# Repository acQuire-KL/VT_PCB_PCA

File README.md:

HISTORY

<table>
  <tr>
    <td valign="top">
      
    </td>
    <td valign="top">
      <table border="1">
        <tr>
          <th style="font-size: 14px; font-weight: bold;">Name</th>
          <th style="font-size: 14px; font-weight: bold;">PCB</th>
          <th style="font-size: 14px; font-weight: bold;">PCA</th>
          <th style="font-size: 14px; font-weight: bold;">Date</th>
          <th style="font-size: 14px; font-weight: bold;">Comments</th>
        </tr>
        <tr>
          
          <td style="font-size: 12px;">ADE</td>
          <td style="font-size: 12px;">4901-30030-05</td>
          <td style="font-size: 12px;">3901-30030-05</td>
          <td style="font-size: 12px;">2024-09-20</td>
          <td style="font-size: 12px;">Current MFG Revisions</td>
        </tr>
        <tr>
          <td style="font-size: 12px;"></td>
          <td style="font-size: 12px;">2025-03-28</td>
          <td style="font-size: 12px;">00 --> 01 to add new circuit sections</td>
        </tr>
        <tr>
          <td style="font-size: 12px;">PCB_1001_00</td>
          <td style="font-size: 12px;">2025-03-01</td>
          <td style="font-size: 12px;">Initial release</td>
        </tr>
      </table>
    </td>
  </tr>
</table>

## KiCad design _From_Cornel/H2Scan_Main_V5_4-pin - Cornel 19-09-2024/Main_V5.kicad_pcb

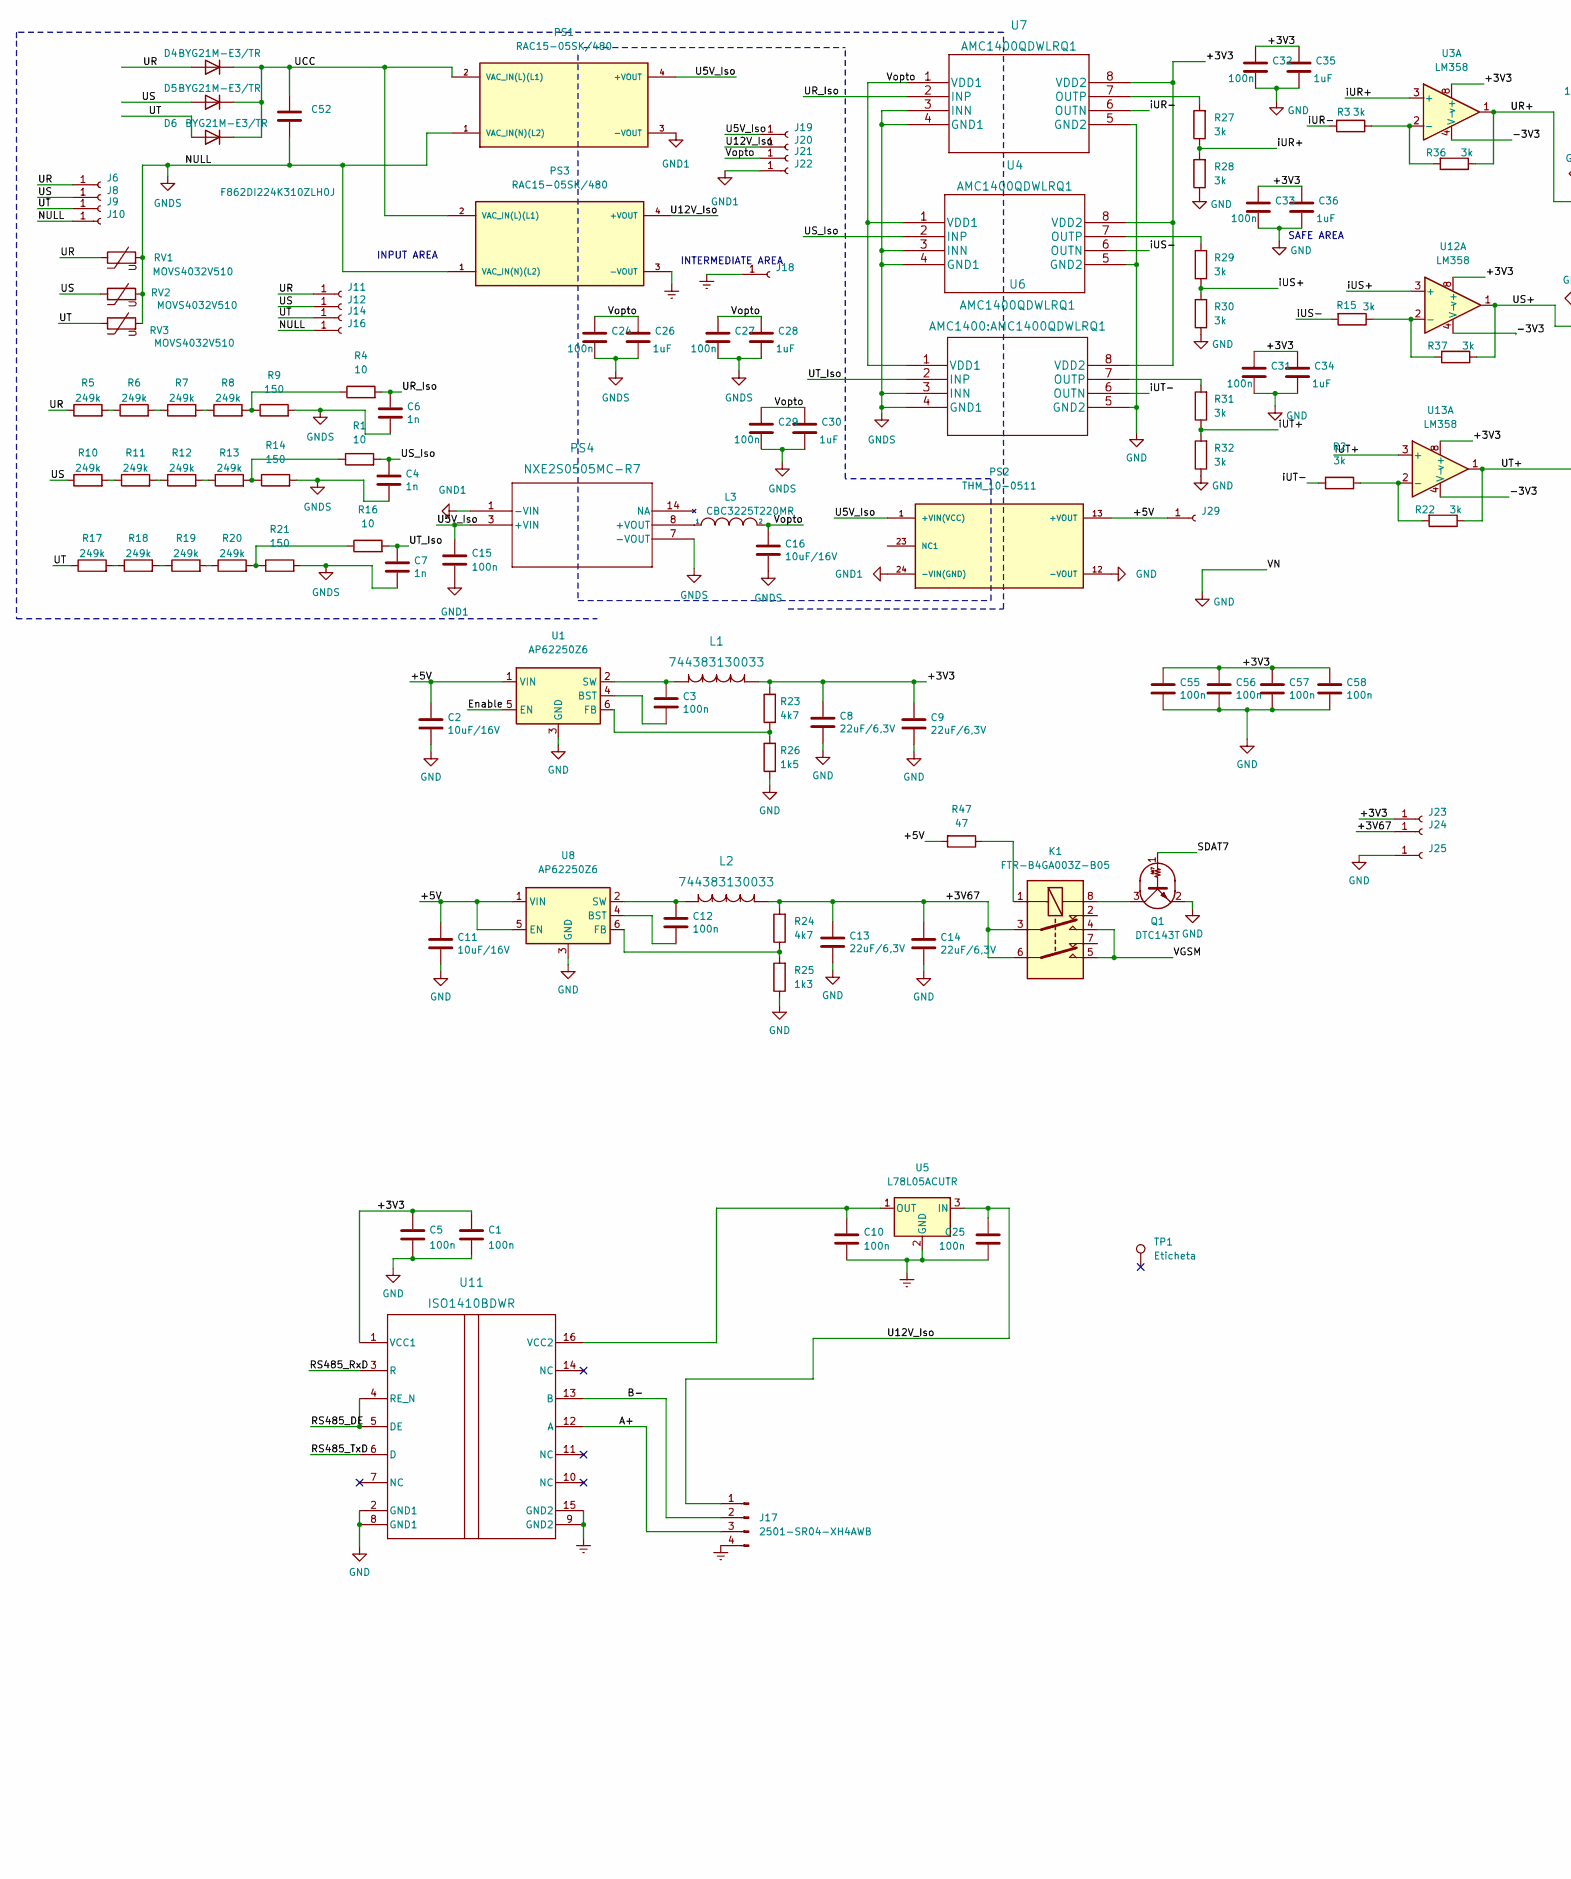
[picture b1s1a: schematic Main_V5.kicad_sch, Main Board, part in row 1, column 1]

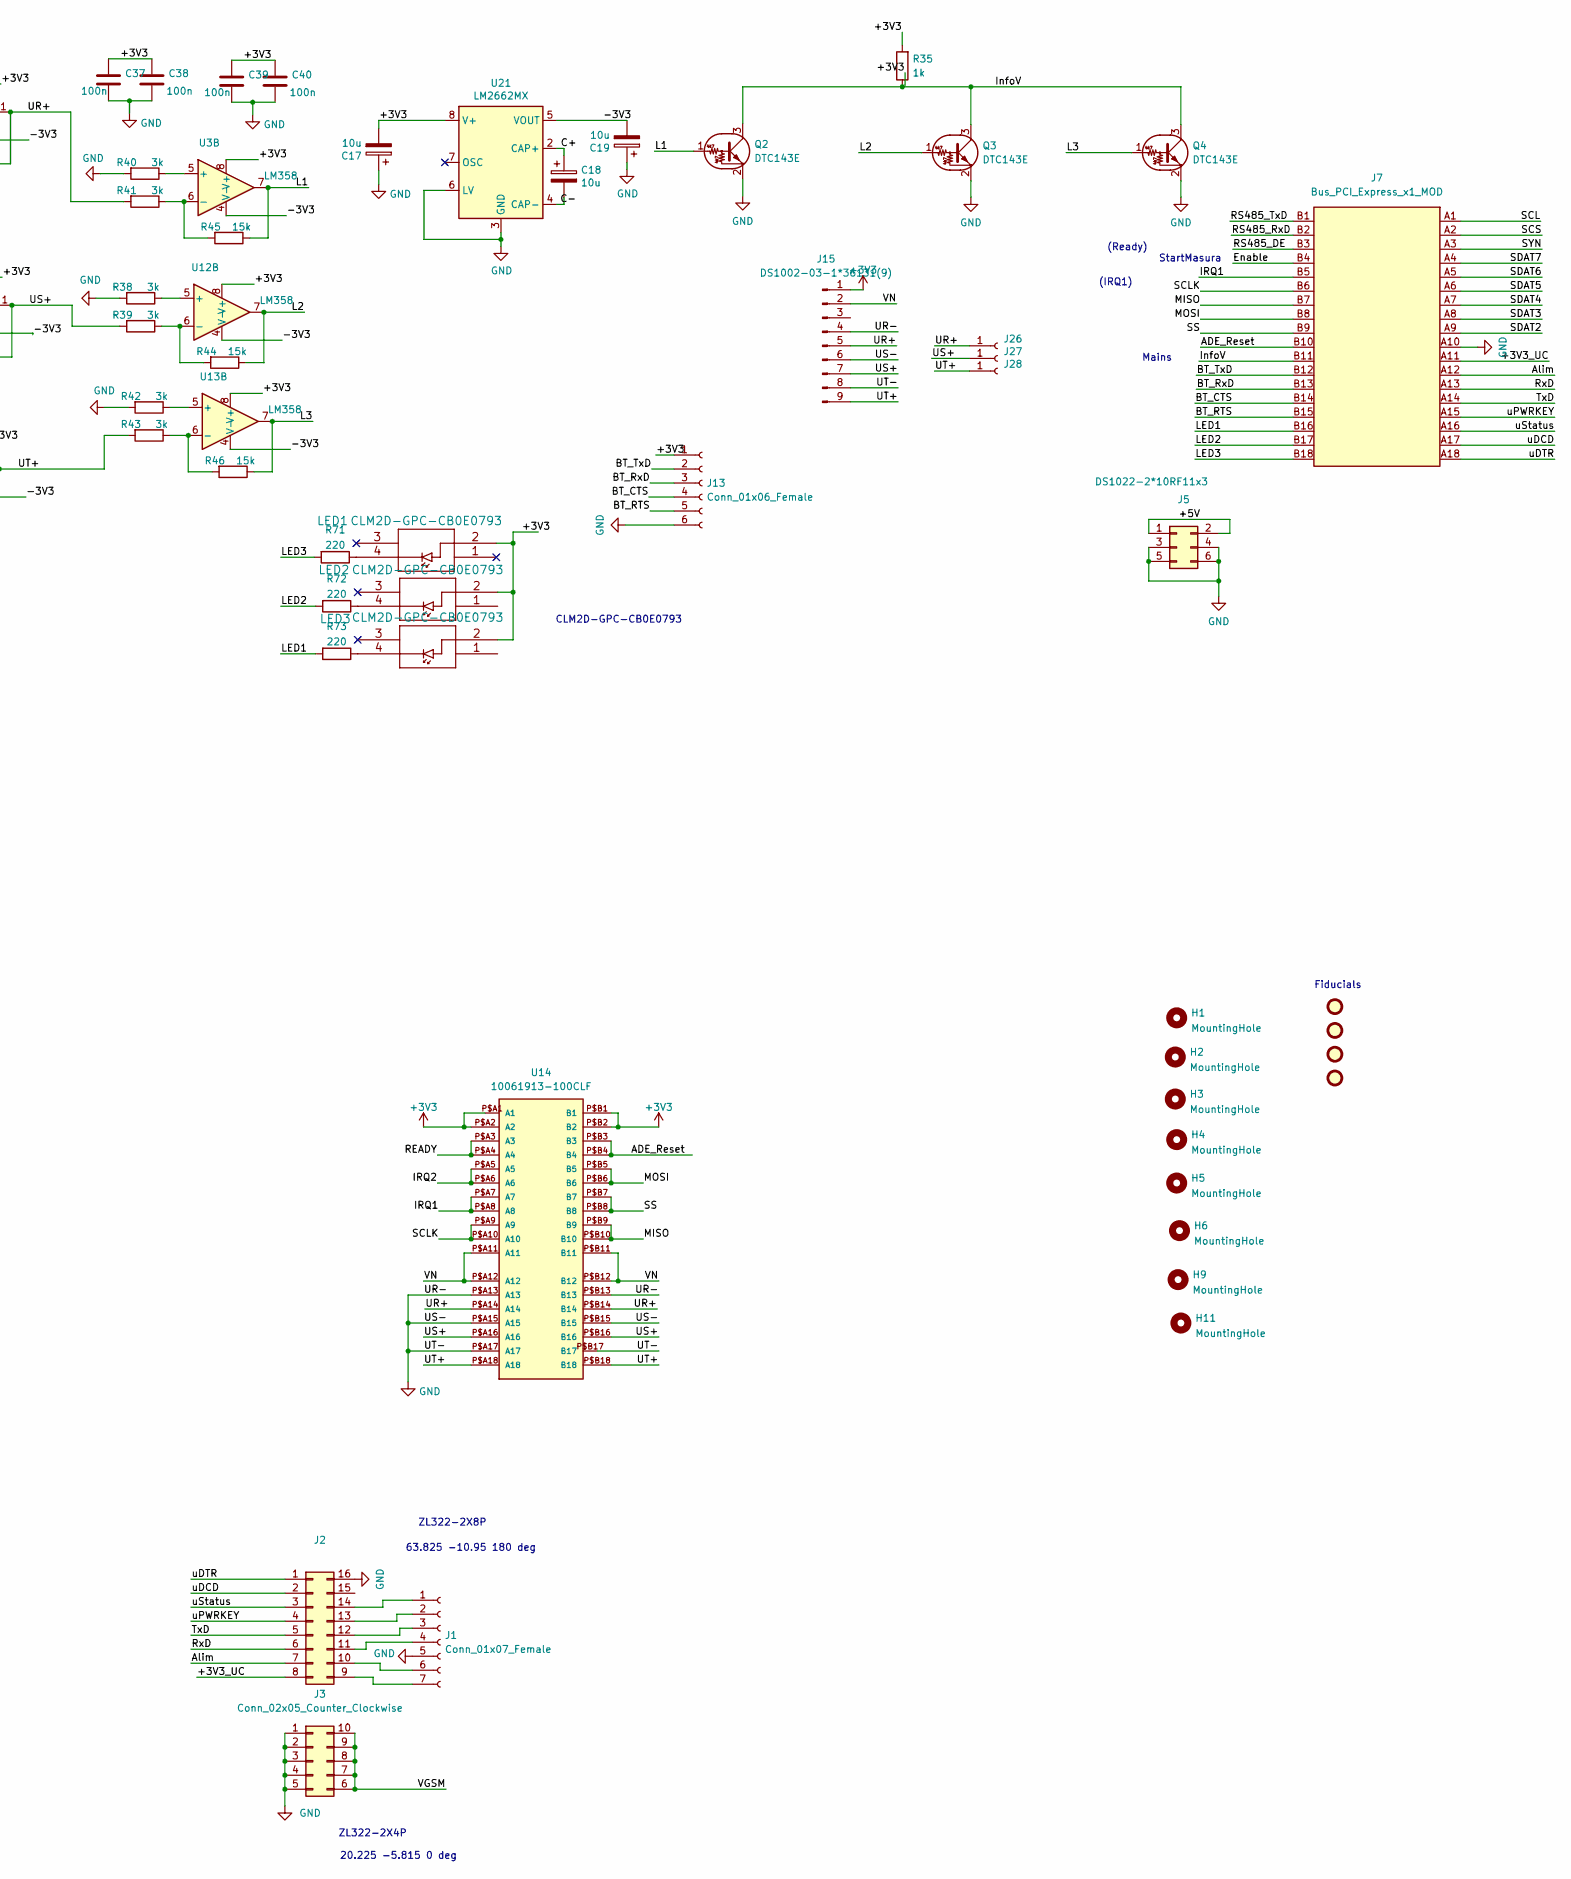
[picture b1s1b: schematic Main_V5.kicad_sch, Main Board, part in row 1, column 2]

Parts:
C1, C3, C5, C10, C12, C15, C24, C25, C27, C29, C31, C32, C33, C37, C38, C39, C40, C55, C56, C57, C58: 100n; C_0603_1608Metric
C2, C11, C16: 10uF/16V; C_1206_3216Metric
C4, C6, C7: 1n; C_0603_1608Metric
C8, C9, C13, C14: 22uF/6,3V; C_1206_3216Metric
C17, C18, C19: 10u; C_1206_3216Metric
C26, C28, C30, C34, C35, C36: 1uF; C_0603_1608Metric
C52: F862DI224K310ZLH0J; C_Rect_L24.0mm_W7.0mm_P22.50mm_MKT
D4, D5, D6: BYG21M-E3/TR; D_SMA
FID1, FID2, FID3, FID4: Fiducial; Fiducial_1mm_Mask2mm
H1, H2, H3, H4, H5, H6, H9, H11: MountingHole; MountingHole_3.2mm_M3
J1: Conn_01x07_Female; PinSocket_1x07_P2.54mm_Vertical
J2: Conn_02x08_Counter_Clockwise; PinSocket_2x08_P2.54mm_Vertical_SMD_MOD
J3: Conn_02x05_Counter_Clockwise; PinSocket_2x05_P2.54mm_Vertical_SMD
J5: DS1022-2*10RF11x3; PinHeader_2x03_P2.54mm_Horizontal
J6: Conn_01x01_Female; DELTA_SolderWire-1.5sqmm_1x01_D1.7mm_OD3.9mm
J7: Bus_PCI_Express_x1_MOD; BUS_PCIexpress_x1
J8, J9, J10: Conn_01x01_Female; DELTA_R_SolderWire-1.5sqmm_1x01_D1.7mm_OD3.9mm
J11, J12, J14, J16, J18, J19, J20, J21, J22, J23, J24, J25, J26, J27, J28, J29: Conn_01x01_Female; TestPoint_Pad_2.5x2.5mm_Delta
J13: Conn_01x06_Female; PinSocket_1x06_P2.54mm_Vertical
J15: DS1002-03-1*36131(9); PinSocket_1x09_P2.54mm_Vertical
J17: 2501-SR04-XH4AWB; A2501-SR04-XH4AWB
K1: FTR-B4GA003Z-B05; Relay_Fujitsu_FTR-B4GA003
L1, L2: 744383130033
L3: CBC3225T220MR; L_1206_3216Metric
LED1, LED2, LED3: CLM2D-GPC-CB0E0793
PS1, PS3: RAC15-05SK/480; CONV_RAC15-12SK_480; PARTREV 0/2022
PS2: THM_10-0511; CONV_THM_10-0511; PARTREV Jan 06, 2021
PS4: NXE2S0505MC-R7; NXE2_SINGLE_SURFACE_MUR
Q1: DTC143T; SOT-23
Q2, Q3, Q4: DTC143E; SOT-23
R1, R4, R16: 10; R_0603_1608Metric
R2, R3, R15, R22, R27, R28, R29, R30, R31, R32, R36, R37, R38, R39, R40, R41, R42, R43: 3k; R_0603_1608Metric
R5, R6, R7, R8, R10, R11, R12, R13, R17, R18, R19, R20: 249k; R_2512_6332Metric
R9, R14, R21: 150; R_0603_1608Metric
R23, R24: 4k7; R_0603_1608Metric
R25: 1k3; R_0603_1608Metric
R26: 1k5; R_0603_1608Metric
R35: 1k; R_0603_1608Metric
R44, R45, R46: 15k; R_0603_1608Metric
R47: 47; R_0603_1608Metric
R71, R72, R73: 220; R_0603_1608Metric
RV1, RV2, RV3: MOVS4032V510; MOVS4032V460
TP1: Eticheta
U1, U8: AP62250Z6; SOT-563
U3, U12, U13: LM358; SO-8_3.9x4.9mm_P1.27mm
U4, U6, U7: AMC1400QDWLRQ1
U5: L78L05ACUTR; SOT-89-3
U11: ISO1410BDWR; DW0016B_HV
U14: 10061913-100CLF; MPN 10061913-100CLF
U21: LM2662MX; SO-8_3.9x4.9mm_P1.27mm

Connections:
+3V3: C1.1, C5.1, C8.1, C9.1, C17.2, C31.1, C32.1, C33.1, C34.1, C35.1, C36.1, C37.1, C38.1, C39.1, C40.1, C55.1, C56.1, C57.1, C58.1, J13.1, J15.1, J23.1, L1.1, LED1.2, LED2.2, LED3.2, R23.2, R35.2, U3.8 (v+), U4.8 (VDD2), U6.8 (VDD2), U7.8 (VDD2), U11.1 (VCC1), U12.8 (v+), U13.8 (v+), U14.P$A1 (A1), U14.P$A2 (A2), U14.P$B1 (B1), U14.P$B2 (B2), U21.8 (V+)
/+3V3_UC: J2.8, J7.A11
/+3V67: C13.1, C14.1, J24.1, K1.3, K1.6, L2.1, R24.2
/+5V: C2.1, C11.1, J5.1, J5.2, J29.1, PS2.13 (+VOUT), R47.2, U1.1 (VIN), U8.1 (VIN), U8.5 (EN)
/-3V3: C19.2, U3.4 (V-), U12.4 (V-), U13.4 (V-), U21.5 (VOUT)
/A+: J17.3, U11.12 (A)
/ADE_Reset: J7.B10, U14.P$B3 (B3), U14.P$B4 (B4)
/Alim: J2.7, J7.A12
/B-: J17.2, U11.13 (B)
/BT_CTS: J7.B14, J13.4
/BT_RTS: J7.B15, J13.5
/BT_RxD: J7.B13, J13.3
/BT_TxD: J7.B12, J13.2
/C+: C18.1, U21.2 (CAP+)
/C-: C18.2, U21.4 (CAP-)
/Enable: J7.B4, U1.5 (EN)
/IRQ1: J7.B5, U14.P$A7 (A7), U14.P$A8 (A8)
/IRQ2: U14.P$A5 (A5), U14.P$A6 (A6)
/InfoV: J7.B11, Q2.3 (C), Q3.3 (C), Q4.3 (C), R35.1
/L1: Q2.1 (B), R45.1, U3.7
/L2: Q3.1 (B), R44.1, U12.7
/L3: Q4.1 (B), R46.1, U13.7
/LED1: J7.B16, R73.2
/LED2: J7.B17, R72.2
/LED3: J7.B18, R71.2
/MISO: J7.B7, U14.P$B9 (B9), U14.P$B10 (B10)
/MOSI: J7.B8, U14.P$B5 (B5), U14.P$B6 (B6)
/READY: U14.P$A3 (A3), U14.P$A4 (A4)
/RS485_DE: J7.B3, U11.4 (RE_N), U11.5 (DE)
/RS485_RxD: J7.B2, U11.3 (R)
/RS485_TxD: J7.B1, U11.6 (D)
/RxD: J2.6, J7.A13
/SCL: J7.A1
/SCLK: J7.B6, U14.P$A9 (A9), U14.P$A10 (A10)
/SCS: J7.A2
/SDAT2: J7.A9
/SDAT3: J7.A8
/SDAT4: J7.A7
/SDAT5: J7.A6
/SDAT6: J7.A5
/SDAT7: J7.A4, Q1.1 (B)
/SS: J7.B9, U14.P$B7 (B7), U14.P$B8 (B8)
/SYN: J7.A3
/TxD: J2.5, J7.A14
/U5V_Iso: C15.1, J19.1, PS1.4 (+VOUT), PS2.1 (+VIN(VCC)), PS4.3 (+VIN)
/U12V_Iso: C25.1, J17.1, J20.1, PS3.4 (+VOUT), U5.3 (IN)
/UCC: C52.1, D4.1 (K), D5.1 (K), D6.1 (K), PS1.2 (VAC_IN(L)(L1)), PS3.2 (VAC_IN(L)(L1))
/UR: D4.2 (A), J6.1, J11.1, R5.1, RV1.1
/UR+: J15.5, J26.1, R36.1, R41.2, U3.1, U14.P$A14 (A14), U14.P$B14 (B14)
/UR_Iso: C6.1, R4.2, U7.2 (INP)
/US: D5.2 (A), J8.1, J12.1, R10.1, RV2.1
/US+: J15.7, J27.1, R37.1, R39.2, U12.1, U14.P$A16 (A16), U14.P$B16 (B16)
/US_Iso: C4.1, R1.2, U4.2 (INP)
/UT: D6.2 (A), J9.1, J14.1, R17.1, RV3.1
/UT+: J15.9, J28.1, R22.1, R43.2, U13.1, U14.P$A18 (A18), U14.P$B18 (B18)
/UT_Iso: C7.1, R16.2, U6.2 (INP)
/VGSM: J3.6, J3.7, J3.8, J3.9, J3.10, K1.4, K1.5
/Vopto: C16.1, C24.1, C26.1, C27.1, C28.1, C29.1, C30.1, J21.1, L3.2, U4.1 (VDD1), U6.1 (VDD1), U7.1 (VDD1)
/iUR+: R27.1, R28.2, U3.3 (+)
/iUR-: R3.2, U7.6 (OUTN)
/iUS+: R29.1, R30.2, U12.3 (+)
/iUS-: R15.2, U4.6 (OUTN)
/iUT+: R31.1, R32.2, U13.3 (+)
/iUT-: R2.2, U6.6 (OUTN)
/uDCD: J2.2, J7.A17
/uDTR: J2.1, J7.A18
/uPWRKEY: J2.4, J7.A15
/uStatus: J2.3, J7.A16
Earth: C10.2, C25.2, J17.4, J18.1, PS3.3 (-VOUT), U5.2 (GND), U11.9 (GND2), U11.15 (GND2)
GND: C1.2, C2.2, C5.2, C8.2, C9.2, C11.2, C13.2, C14.2, C17.1, C19.1, C31.2, C32.2, C33.2, C34.2, C35.2, C36.2, C37.2, C38.2, C39.2, C40.2, C55.2, C56.2, C57.2, C58.2, J1.5, J2.16, J3.1, J3.2, J3.3, J3.4, J3.5, J5.3, J5.4, J5.5, J5.6, J7.A10, J13.6, J15.2, J15.4, J15.6, J15.8, J25.1, PS2.12 (-VOUT), Q1.2 (E), Q2.2 (E), Q3.2 (E), Q4.2 (E), R25.1, R26.1, R28.1, R30.1, R32.1, R38.2, R40.2, R42.2, U1.3 (GND), U4.5 (GND2), U6.5 (GND2), U7.5 (GND2), U8.3 (GND), U11.2 (GND1), U11.8 (GND1), U14.P$A11 (A11), U14.P$A12 (A12), U14.P$A13 (A13), U14.P$A15 (A15), U14.P$A17 (A17), U14.P$B11 (B11), U14.P$B12 (B12), U14.P$B13 (B13), U14.P$B15 (B15), U14.P$B17 (B17), U21.3 (GND), U21.6 (LV)
GND1: C15.2, J22.1, PS1.3 (-VOUT), PS2.24 (-VIN(GND)), PS4.1 (-VIN)
GNDS: C4.2, C6.2, C7.2, C16.2, C24.2, C26.2, C27.2, C28.2, C29.2, C30.2, C52.2, J10.1, J16.1, PS1.1 (VAC_IN(N)(L2)), PS3.1 (VAC_IN(N)(L2)), PS4.7 (-VOUT), R9.2, R14.2, R21.2, RV1.2, RV2.2, RV3.2, U4.3 (INN), U4.4 (GND1), U6.3 (INN), U6.4 (GND1), U7.3 (INN), U7.4 (GND1)
unnamed: J1.1, J2.14
unnamed: J1.2, J2.13
unnamed: J1.3, J2.12
unnamed: J1.4, J2.11
unnamed: J1.6, J2.10
unnamed: J1.7, J2.9
unnamed: K1.1, R47.1
unnamed: LED1.4, R71.1
unnamed: LED2.4, R72.1
unnamed: LED3.4, R73.1
unnamed: L3.1, PS4.8 (+VOUT)
unnamed: K1.8, Q1.3 (C)
unnamed: R1.1, R13.2, R14.1
unnamed: R4.1, R8.2, R9.1
unnamed: R5.2, R6.1
unnamed: R6.2, R7.1
unnamed: R7.2, R8.1
unnamed: R10.2, R11.1
unnamed: R11.2, R12.1
unnamed: R12.2, R13.1
unnamed: R16.1, R20.2, R21.1
unnamed: R17.2, R18.1
unnamed: R18.2, R19.1
unnamed: R19.2, R20.1
unnamed: C3.2, U1.4 (BST)
unnamed: R23.1, R26.2, U1.6 (FB)
unnamed: C3.1, L1.2, U1.2 (SW)
unnamed: R3.1, R36.2, U3.2 (-)
unnamed: R40.1, U3.5 (+)
unnamed: R41.1, R45.2, U3.6 (-)
unnamed: R29.2, U4.7 (OUTP)
unnamed: R31.2, U6.7 (OUTP)
unnamed: R27.2, U7.7 (OUTP)
unnamed: C12.2, U8.4 (BST)
unnamed: R24.1, R25.2, U8.6 (FB)
unnamed: C12.1, L2.2, U8.2 (SW)
unnamed: C10.1, U5.1 (OUT), U11.16 (VCC2)
unnamed: R15.1, R37.2, U12.2 (-)
unnamed: R38.1, U12.5 (+)
unnamed: R39.1, R44.2, U12.6 (-)
unnamed: R2.1, R22.2, U13.2 (-)
unnamed: R42.1, U13.5 (+)
unnamed: R43.1, R46.2, U13.6 (-)

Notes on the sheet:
ZL322-2X4P
ZL322-2X8P
20.225 -5.815 0 deg
(Ready)
Fiducials
Mains
(IRQ1)
CLM2D-GPC-CB0E0793
StartMasura
63.825 -10.95 180 deg
SAFE AREA
INPUT AREA
INTERMEDIATE AREA

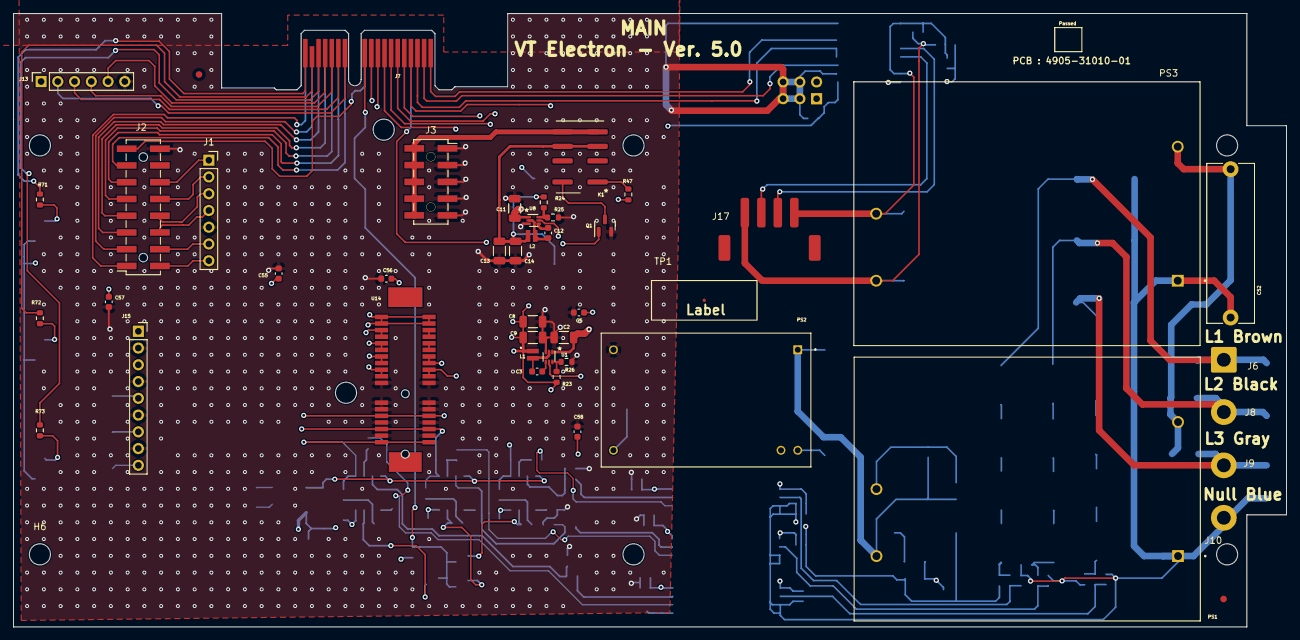
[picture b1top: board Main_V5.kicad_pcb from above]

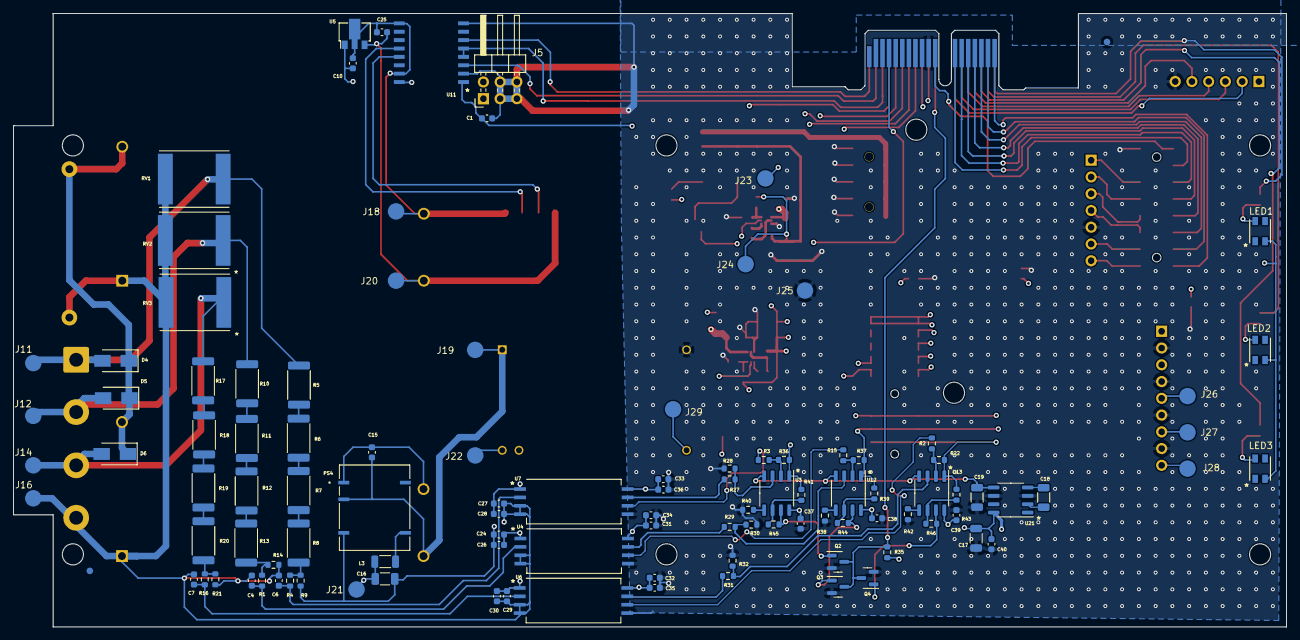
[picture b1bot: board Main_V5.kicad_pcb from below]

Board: 4 copper layers, 193.0 x 93.0 mm, 163 parts (109 on the bottom side), 107 nets.

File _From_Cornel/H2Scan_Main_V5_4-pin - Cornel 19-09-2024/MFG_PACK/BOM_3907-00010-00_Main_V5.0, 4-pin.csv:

"Reference","VTPN","Value","Datasheet","Footprint","Qty","DNP"
"C1,C3,C5,C10,C12,C15,C24,C25,C27,C29,C31,C32,C33,C37,C38,C39,C40,C55,C56,C57,C58","4106-00020-00","100n","~","Capacitor_SMD:C_0603_1608Metric","21",""
"C2,C11,C16","4112-00100-00","10uF/16V","~","Capacitor_SMD:C_1206_3216Metric","3",""
"C4,C6,C7","4106-00030-00","1n","~","Capacitor_SMD:C_0603_1608Metric","3",""
"C8,C9,C13,C14","4112-00150-00","22uF/6,3V","~","Capacitor_SMD:C_1206_3216Metric","4",""
"C17,C18,C19","4112-00110-00","10u","~","Capacitor_SMD:C_1206_3216Metric","3",""
"C26,C28,C30,C34,C35,C36","4106-00100-00","1uF","~","Capacitor_SMD:C_0603_1608Metric","6",""
"C52","4130-00010-00","F862DI224K310ZLH0J","~","Capacitor_THT:C_Rect_L24.0mm_W7.0mm_P22.50mm_MKT","1",""
"D4,D5,D6","4510-00010-00","BYG21M-E3/TR","~","Diode_SMD:D_SMA","3",""
"FID1,FID2,FID3,FID4","4000-00000-00","Fiducial","~","Fiducial:Fiducial_1mm_Mask2mm","4",""
"H1,H2,H3,H4,H5,H6,H9,H11","4000-00000-00","MountingHole","~","MountingHole:MountingHole_3.2mm_M3","8",""
"J1","4401-00070-00","Conn_01x07_Female","~","Connector_PinSocket_2.54mm:PinSocket_1x07_P2.54mm_Vertical","1",""
"J2","4402-10021-00","Conn_02x08_Counter_Clockwise","~","Connector_PinSocket_2.54mm:PinSocket_2x08_P2.54mm_Vertical_SMD_MOD","1",""
"J3","4402-10011-00","Conn_02x05_Counter_Clockwise","~","Connector_PinSocket_2.54mm:PinSocket_2x05_P2.54mm_Vertical_SMD","1",""
"J5","4400-00010-00","DS1022-2*10RF11x3","~","Connector_PinHeader_2.54mm:PinHeader_2x03_P2.54mm_Horizontal","1",""
"J6,J8,J9,J10,J11,J12,J14,J16,J18,J19,J20,J21,J22,J23,J24,J25,J26,J27,J28,J29","4000-00000-00","Conn_01x01_Female","~","-- mixed values --","20",""
"J7","4000-00000-00","Bus_PCI_Express_x1_MOD","http://www.ritrontek.com/uploadfile/2016/1026/20161026105231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","Connector_PCBEdge:BUS_PCIexpress_x1","1",""
"J13","4401-00050-00","Conn_01x06_Female","~","Connector_PinSocket_2.54mm:PinSocket_1x06_P2.54mm_Vertical","1",""
"J15","4401-00060-00","DS1002-03-1*36131(9)","~","Connector_PinSocket_2.54mm:PinSocket_1x09_P2.54mm_Vertical","1",""
"J17","4408-00030-00","2501-SR04-XH4AWB","~","Connector_JST:A2501-SR04-XH4AWB","1",""
"K1","4750-00010-00","FTR-B4GA003Z-B05","https://www.fujitsu.com/downloads/MICRO/fcai/relays/ftr-f1.pdf","Relay_SMD:Relay_Fujitsu_FTR-B4GA003","1",""
"L1,L2","4300-00010-00","744383130033","","Inductanta744:744383130033","2",""
"L3","4300-00020-00","CBC3225T220MR","~","Inductor_SMD:L_1206_3216Metric","1",""
"LED1,LED2,LED3","4752-00010-00","CLM2D-GPC-CB0E0793","","LedSMD_Cree:CLM2D-GPC-CB0E0793","3",""
"PS1,PS3","4520-30010-00","RAC15-05SK/480","","RAC15:CONV_RAC15-12SK_480","2",""
"PS2","4520-20010-00","THM_10-0511","","THM 10-0511:CONV_THM_10-0511","1",""
"PS4","4520-20022-00","NXE2S0505MC-R7","NXE2S0505MC-R7","NXE2S0505MC-R7:NXE2_SINGLE_SURFACE_MUR","1",""
"Q1","4500-00020-00","DTC143T","","Package_TO_SOT_SMD:SOT-23","1",""
"Q2,Q3,Q4","4500-00010-00","DTC143E","","Package_TO_SOT_SMD:SOT-23","3",""
"R1,R4,R16","4006-00030-00","10","~","Resistor_SMD:R_0603_1608Metric","3",""
"R2,R3,R15,R22,R27,R28,R29,R30,R31,R32,R36,R37,R38,R39,R40,R41,R42,R43","4006-00300-00","3k","~","Resistor_SMD:R_0603_1608Metric","18",""
"R5,R6,R7,R8,R10,R11,R12,R13,R17,R18,R19,R20","4018-01000-00","249k","~","Resistor_SMD:R_2512_6332Metric","12",""
"R9,R14,R21","4006-00040-00","150","~","Resistor_SMD:R_0603_1608Metric","3",""
"R23,R24","4006-00150-00","4k7","~","Resistor_SMD:R_0603_1608Metric","2",""
"R25","4006-00130-00","1k3","~","Resistor_SMD:R_0603_1608Metric","1",""
"R26","4006-00140-00","1k5","~","Resistor_SMD:R_0603_1608Metric","1",""
"R35","4006-00100-00","1k","~","Resistor_SMD:R_0603_1608Metric","1",""
"R44,R45,R46","4006-00160-00","15k","~","Resistor_SMD:R_0603_1608Metric","3",""
"R47","4006-00010-00","47","~","Resistor_SMD:R_0603_1608Metric","1",""
"R71,R72,R73","4006-00020-00","220","~","Resistor_SMD:R_0603_1608Metric","3",""
"RV1,RV2,RV3","4022-00010-00","MOVS4032V510","~","MOVS4032V510:MOVS4032V460","3",""
"TP1","4000-00000-00","Eticheta","~","Symbol:Eticheta","1",""
"U1,U8","4520-10010-00","AP62250Z6","https://www.diodes.com/assets/Datasheets/AP62250.pdf","Package_TO_SOT_SMD:SOT-563","2",""
"U3,U12,U13","4708-00021-00","LM358","http://www.ti.com/lit/ds/symlink/lm2904-n.pdf","Package_SO:SO-8_3.9x4.9mm_P1.27mm","3",""
"U4,U6,U7","4710-00010-00","AMC1400QDWLRQ1","","AMC1400:AMC1400QDWLRQ1","3",""
"U5","4522-00010-00","L78L05ACUTR","http://www.st.com/content/ccc/resource/technical/document/da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","Package_TO_SOT_SMD:SOT-89-3","1",""
"U11","4700-00020-00","ISO1410BDWR","ISO1410BDWR","ISO1410:DW0016B_HV","1",""
"U14","4410-00010-00","10061913-100CLF","","PCI_SMD_MOD:10061913-100CLF","1",""
"U21","4520-00020-01","LM2662MX","http://www.ti.com/lit/ds/symlink/lmc7660.pdf","Package_SO:SO-8_3.9x4.9mm_P1.27mm","1",""

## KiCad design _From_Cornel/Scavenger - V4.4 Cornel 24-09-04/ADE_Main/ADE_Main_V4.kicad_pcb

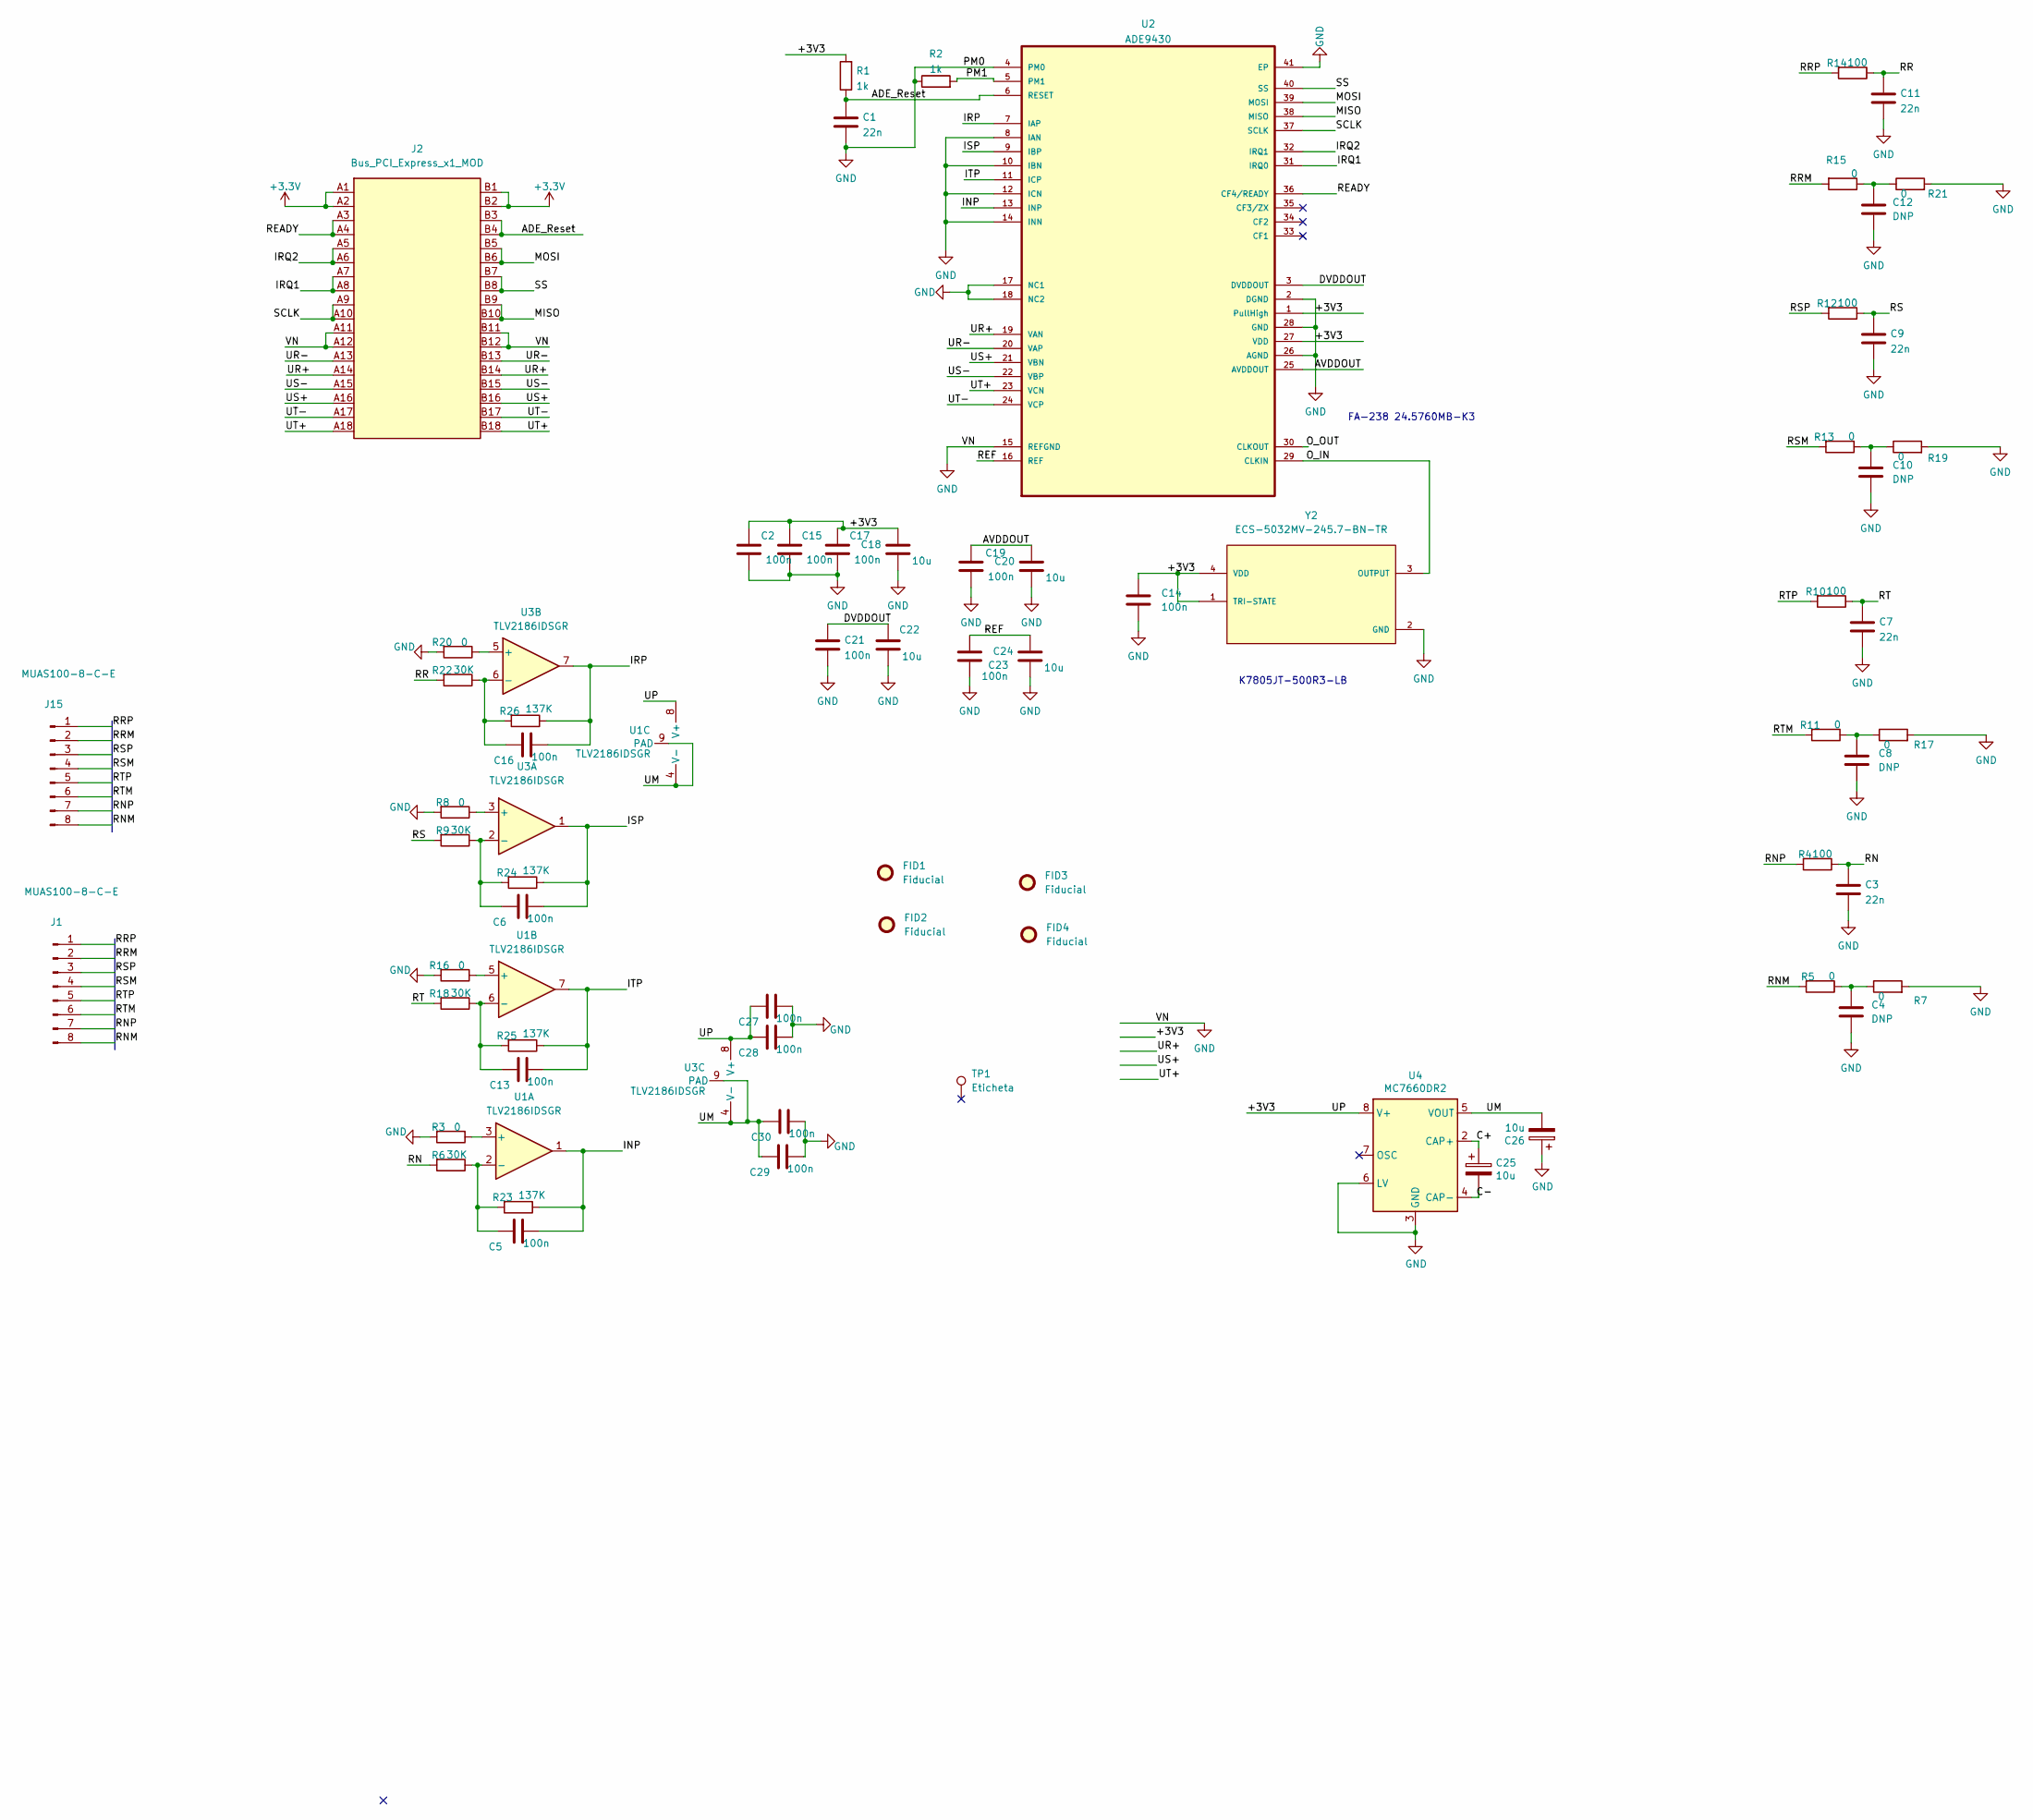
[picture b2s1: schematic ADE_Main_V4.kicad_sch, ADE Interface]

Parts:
C1, C3, C7, C9, C11: 22n; C_0402_1005Metric
C2: 100n; C_0603_1608Metric
C4, C8, C10, C12: DNP; C_0402_1005Metric
C5, C6, C13, C14, C15, C16, C17, C19, C21, C23, C27, C28, C29, C30: 100n; C_0402_1005Metric
C18, C20, C22, C24, C25, C26: 10u; C_1206_3216Metric
FID1, FID2, FID3, FID4: Fiducial; Fiducial_1mm_Mask2mm
J1: MUAS100-8-C-E; A2501-SR08-XH8AWB
J2: Bus_PCI_Express_x1_MOD; BUS_PCIexpress_x1
J15: MUAS100-8-C-E; PinHeader_1x08_P2.54mm_Vertical
R1, R2: 1k; R_0402_1005Metric
R3, R5, R7, R8, R11, R13, R15, R16, R17, R19, R20, R21: 0; R_0402_1005Metric
R4, R10, R12, R14: 100; R_0402_1005Metric
R6, R9, R18, R22: 30K; R_0402_1005Metric
R23, R24, R25, R26: 137K; R_0402_1005Metric
TP1: Eticheta
U1, U3: TLV2186IDSGR; WSON-8-1EP_2x2mm_P0.5mm_EP0.9x1.6mm_ThermalVias
U2: ADE9430; MPN AD9115BCPZ
U4: MC7660DR2; SO-8_3.9x4.9mm_P1.27mm
Y2: ECS-5032MV-245.7-BN-TR; OSC_ECS-5032MV-245.7-BN-TR

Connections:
/ADE_Reset: C1.1, J2.B3, J2.B4, R1.1, U2.6 (RESET)
/AVDDOUT: C19.1, C20.1, U2.25 (AVDDOUT)
/C+: C25.1, U4.2 (CAP+)
/C-: C25.2, U4.4 (CAP-)
/DVDDOUT: C21.1, C22.1, U2.3 (DVDDOUT)
/INP: C5.1, R23.1, U1.1, U2.13 (INP)
/IRP: C16.1, R26.1, U2.7 (IAP), U3.7
/IRQ1: J2.A7, J2.A8, U2.31 (IRQ0)
/IRQ2: J2.A5, J2.A6, U2.32 (IRQ1)
/ISP: C6.1, R24.1, U2.9 (IBP), U3.1
/ITP: C13.1, R25.1, U1.7, U2.11 (ICP)
/MISO: J2.B9, J2.B10, U2.38 (MISO)
/MOSI: J2.B5, J2.B6, U2.39 (MOSI)
/O_IN: U2.29 (CLKIN), Y2.3 (OUTPUT)
/O_OUT: U2.30 (CLKOUT)
/PM1: R2.2, U2.5 (PM1)
/READY: J2.A3, J2.A4, U2.36 (CF4/READY)
/REF: C23.1, C24.1, U2.16 (REF)
/RN: C3.1, R4.1, R6.2
/RNM: J1.8, J15.8, R5.2
/RNP: J1.7, J15.7, R4.2
/RR: C11.1, R14.1, R22.2
/RRM: J1.2, J15.2, R15.2
/RRP: J1.1, J15.1, R14.2
/RS: C9.1, R9.2, R12.1
/RSM: J1.4, J15.4, R13.2
/RSP: J1.3, J15.3, R12.2
/RT: C7.1, R10.1, R18.2
/RTM: J1.6, J15.6, R11.2
/RTP: J1.5, J15.5, R10.2
/SCLK: J2.A9, J2.A10, U2.37 (SCLK)
/SS: J2.B7, J2.B8, U2.40 (SS)
/UM: C26.2, C29.2, C30.2, U1.4 (V-), U1.9 (PAD), U3.4 (V-), U3.9 (PAD), U4.5 (VOUT)
/UR+: J2.A14, J2.B14, U2.19 (VAN)
/UR-: J2.A13, J2.B13, U2.20 (VAP)
/US+: J2.A16, J2.B16, U2.21 (VBN)
/US-: J2.A15, J2.B15, U2.22 (VBP)
/UT+: J2.A18, J2.B18, U2.23 (VCN)
/UT-: J2.A17, J2.B17, U2.24 (VCP)
GND: C1.2, C2.2, C3.2, C4.2, C7.2, C8.2, C9.2, C10.2, C11.2, C12.2, C14.2, C15.2, C17.2, C18.2, C19.2, C20.2, C21.2, C22.2, C23.2, C24.2, C26.1, C27.1, C28.1, C29.1, C30.1, J2.A11, J2.A12, J2.B11, J2.B12, R2.1, R3.2, R7.2, R8.2, R16.2, R17.2, R19.2, R20.2, R21.2, U2.2 (DGND), U2.4 (PM0), U2.8 (IAN), U2.10 (IBN), U2.12 (ICN), U2.14 (INN), U2.15 (REFGND), U2.17 (NC1), U2.18 (NC2), U2.26 (AGND), U2.28 (GND), U2.41 (EP), U4.3 (GND), U4.6 (LV), Y2.2 (GND)
unnamed: C4.1, R5.1, R7.1
unnamed: C5.2, R6.1, R23.2, U1.2 (-)
unnamed: C6.2, R9.1, R24.2, U3.2 (-)
unnamed: C8.1, R11.1, R17.1
unnamed: C10.1, R13.1, R19.1
unnamed: C12.1, R15.1, R21.1
unnamed: C13.2, R18.1, R25.2, U1.6 (-)
unnamed: C16.2, R22.1, R26.2, U3.6 (-)
unnamed: R3.1, U1.3 (+)
unnamed: R8.1, U3.3 (+)
unnamed: R16.1, U1.5 (+)
unnamed: R20.1, U3.5 (+)

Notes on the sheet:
FA-238 24.5760MB-K3
K7805JT-500R3-LB

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
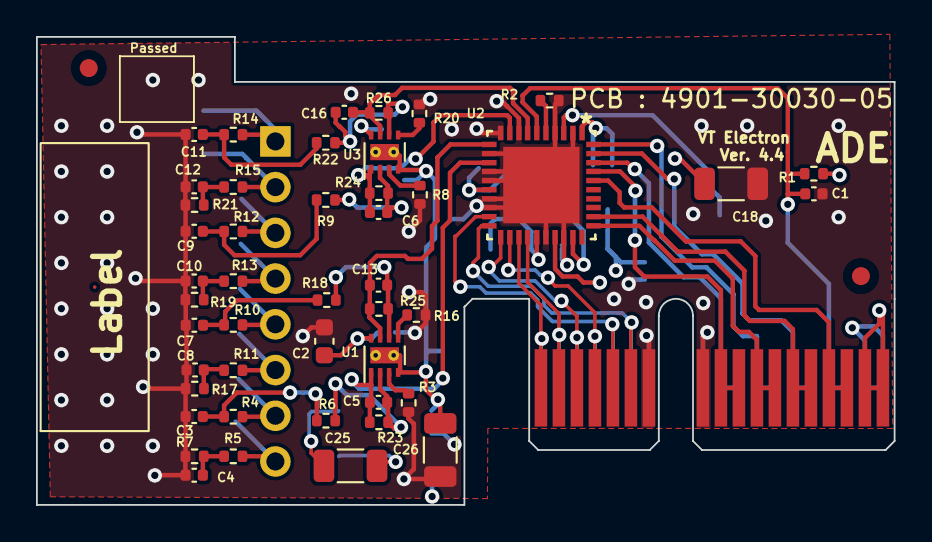
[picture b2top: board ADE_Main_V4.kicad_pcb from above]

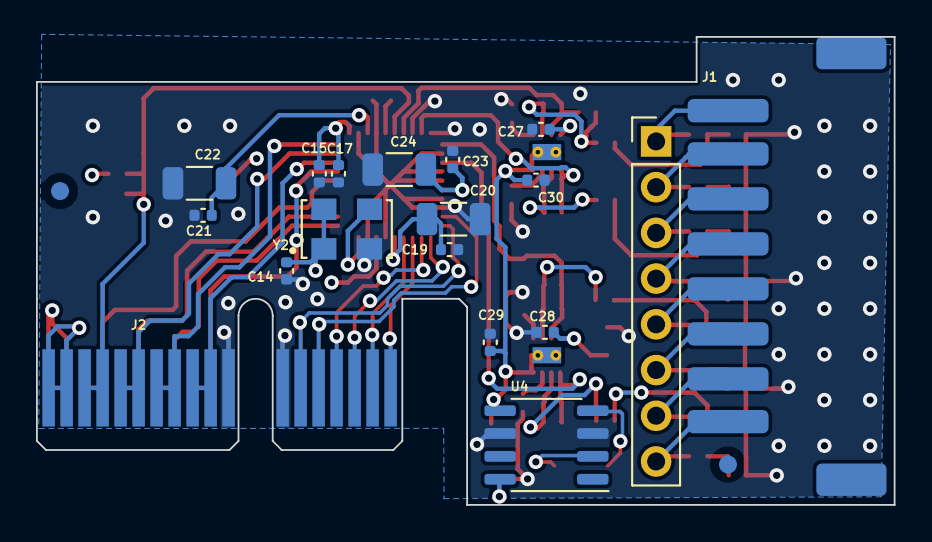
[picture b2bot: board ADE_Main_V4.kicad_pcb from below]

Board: 4 copper layers, 47.6 x 26.0 mm, 69 parts (20 on the bottom side), 52 nets.

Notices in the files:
parts and their libraries:
Copyright 2021 Accelerated Designs. All rights reserved.
